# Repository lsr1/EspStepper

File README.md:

# EspStepper

control a [NEMA stepper motor](https://en.wikipedia.org/wiki/Stepper_motor#NEMA_stepper_motors) with [Home Assistant](https://www.home-assistant.io/) using a D1 mini via [ESPHome](https://esphome.io/). 

## Executive Summary
* This project provides a solution for controlling a NEMA stepper motor with Home Assistant (via ESPHome), utilizing a D1 mini board.
* This project consists of a KiCad project that gives you the [Gerber files](gerber/gerber.zip) to order a PCB (e.g. at [JLCPCB](https://cart.jlcpcb.com) onto which (mostly) passive components (pinheaders/sockets) are soldered. Then you plug on some standard modules you can get from [AliExpress](https://www.aliexpress.com), create a device in Home Assistant and are pretty much done.
* For the impatient: Go to [Installation](#Installation).

## Picture

## Sidenotes
This is my second "public GitHub" project (see here my [first one](https://github.com/lsr1/wb2s-to-esp12)). I made something (crude) that I nevertheless think might be useful for somebody else. That is also the reason why this readme will be very long - for myself I want to document the story behind it for my records, and (hopefully) for your pleasure :-) </br>
Despite the verbosity of the README, it assumes that you know how to solder, how to work with a multi meter and your way around Home Assistant and ESPHome. Some things here are weirdly specific, while some are infuriatingly generic (assuming a lot of knowhow).

## Preamble (Why)
* I did this because I wanted an easy way to drive a stepper via Home Assistant. I couldn't find an idiot-proof end2end solution on the whole internet - everything was just pieces. There was just no "easy" way with   all the parts connected (be it SW or HW). So I made <i>this</i>.
* I did this to scratch an itch of mine, and to hone my skills in all the tools along the toolchain. For me, this was really interdisciplinary. 

## Design Decisions (and other reasoning)
### Goals
* Drive exactly one NEMA stepper.
* Have only one input voltage that works for the stepper but also powers the rest of the board. 
* Have mainly only passive components on the PCB to make it easy to solder.
* Use as many widely available off-the-shelf components and modules as possible over working directly with parts/MCUs.
* Have a compact PCB design.
* Don't use jumpers for MS1/2/3 but solder-bridges (uses less space).
* There are already 3 voltages on the board - make them available.
* Enable usage of unused D1 mini pins via pinheaders.
* Have enough GND pins. 
* Have short high-voltage tracks.
* Have everything socketed. 
* Have the antenna of the D1 board protrude over the PCB to avoid interference from PCB copper fill (I didn't want to create a keep-out zone; not for a specific reason - I just wanted to make due w/o one). 
* The silkscreen on the board shall be self-speaking for modules over the usual 'short nomenclature' (e.g. "J1"). 
* C1 for stabilizing voltage when the NEMA stepper turns on should be optional. 
* No SMD components (to make it easier to solder for novices).
* Voltage pins are intentionally not on one continuous pin row but 3x2.
* Low cost.

### Non-goals
* No need for perfectly aligned mounting holes.
* No need for silent steppers (thus use A4988). 
* Micro-USB port of the D1 does not need to be available when socketed.
* No need for energy efficiency. 
* No need for "perfect" PCB/circuit design (<i>done is better than perfect</i>).

## BOM (for 1 module)
* 1 x PCB (see [Installation](#Installation))
* 1 x D1 Mini (with normal pinheaders looking 'down'; from Ali)
* 1 x A4988 stepper driver (from Ali)
* 1 x MP1584 DC-DC step-down Module with LM2596 (from Ali)
* 1 x KF301- 2Pin 5.0mm screw-terminal (from Ali)
* 4 x 1x8pin female pinheaders 2.54 mm (from Ali)
* 4 x 1x2pin female pinheaders 2.54 mm (from Ali)
* standard 1 row 2.54mm male pinheaders
* (optional) 1 x capacitor (>= 12V, THT radial D5.0mm / P2.00mm)

## Installation
This will be long. Brace.

### Order PCBs
* Go to [JLCPCB](https://cart.jlcpcb.com/quote) and upload the [gerber.zip](gerber/gerber.zip). Sidenote: I'm neither sponsored nor do I endorse them specifically, I just find them convenient. Make sure you select the correct PCB thickness (1.2 mm). I also set "Remove Order Number" to "Specify a location" (layout contains a field for this). No other special settings.

### Soldering
* Solder the components. No special advice here - it should be pretty straight forward.
* Close the MS1/2/3 solder bridges for microstepping.
* If you populate the C1 capacitor, make sure you leave enough 'height' of the legs to fold it down 90 degrees to lie flat (otherwise the A4988 won't fit above).

### Tuning
* <b>BEFORE</b> putting on all modules and connect power, tune the MP1584 to 5V output. Do this <b>now</b>.
* The A4988 needs to be tuned to output the correct voltage for your NEMA stepper. I will not document here how to do this - please google it. 

### Assemply
* Put all modules on the board. Take care of the orientation - there is absolutely no safeguard against voltage reversal or such things.
* Usually an A4988 stepper comes with a mini-heatsink. Put it on.
* Provide 12V input (VCC is left on the screw terminal, GND is right).
* If your NEMA stepper cable is connected [like this](photos/NEMA_cabling.png), then the pins go on the board like shown in the table below (however: don't trust this - your stepper might be different, your cable might be different, etc.):

|row #|color|board pin|
---| --- | ---
1|BLK|2B
2|BLU|2A
3|GRN|1B
4|RED|1A

### Software
* It is assumed you have a working instance of Home Assistant with a working ESPHome plugin. If not, please google how to get there.
* Create an ESPHome device in Home Assistant with the configuration as basis noted in [this file](HomeAssistant/my-stepper.yaml). Modify to your gusto.
* Create an automation in Home Assistant with the configuration noted in [this file](HomeAssistant/automation.yaml). Modify to your gusto. Note: The automation includes a slider control that is not documented here. For POC, just run the automation manually.
* If you run the automation (manually), your stepper should turn.
* Read up on the parameters and play around with them - I am intentionally not providing more info or limits or the like. 

### Caveats / FAQ
* This is not the work of a professional, and thus has not been load/fuzzy/destructive-tested. All things could happen, thus this project comes without any warranty. Never use it anywhere in a production situation.

* You can't solder the MP1584 directly on the board even if you don't care about the mouting-hole: The holes for the pins are too small (only the female pin-headers fit, but no the male pinheaders directly). This might be changed on a v2 of the board.

* Todo for v2: Mark the GND pin for the A4988 with silkscreen on the PCB to make it easier to plug in.

* Todo for v2: Mark the diameter of the mounting holes with silkscreen on the PCB. Saves reaching for the caliper.

* Before publishing I got feedback from some dear friends to put ferrit-pearls in series to the 5V for the A4988 and the D1 to make sure the voltage is "clean". I consciously omitted that feedback for simplicity reasons.

* The mounting holes are connected to GND because ... no reason. 

* There is intentionally no ESPHome binary provided for download and flashing here.

* I'm neither affiliated with nor do I get money from JLC nor Ali, I just find both convenient. 

* Why is there no YT video describing this whole thing? - B/c IMHO YT sucks for technical documentation. 

* The KiCad project does not have all components/footprints - I got them from various online sources and didn't track the copyright - sorry.
* I would love to have some useful web GUI in the ESPHome code - but I don't know how to do that. 

## License and Legalese
* May be (re)used for personal/private use only and not sold/licensed for commercial or financial gain. This non-standard license should make it impossible and really difficult for commercial enterprises to profit from my work (pay people to design this!), but enable the hobbyist/enthusiast to work with it.
* If I have inadverently (re-)used your work without either properly attributing it or something, please let me know - I'd be happy to correct this.

## Donations
Yes please.

## Feedback
Also yes please! (I hope I figure out how this whole pull-request thing works...)

## Shoutout ...
* ... to [CCC](https://www.ccc.de) and [CCCZH](https://www.ccczh.ch/)!
* ... to all FOSS contributors that helped making SW that enabled me to do this. Nanos gigantium humeris insidentes.

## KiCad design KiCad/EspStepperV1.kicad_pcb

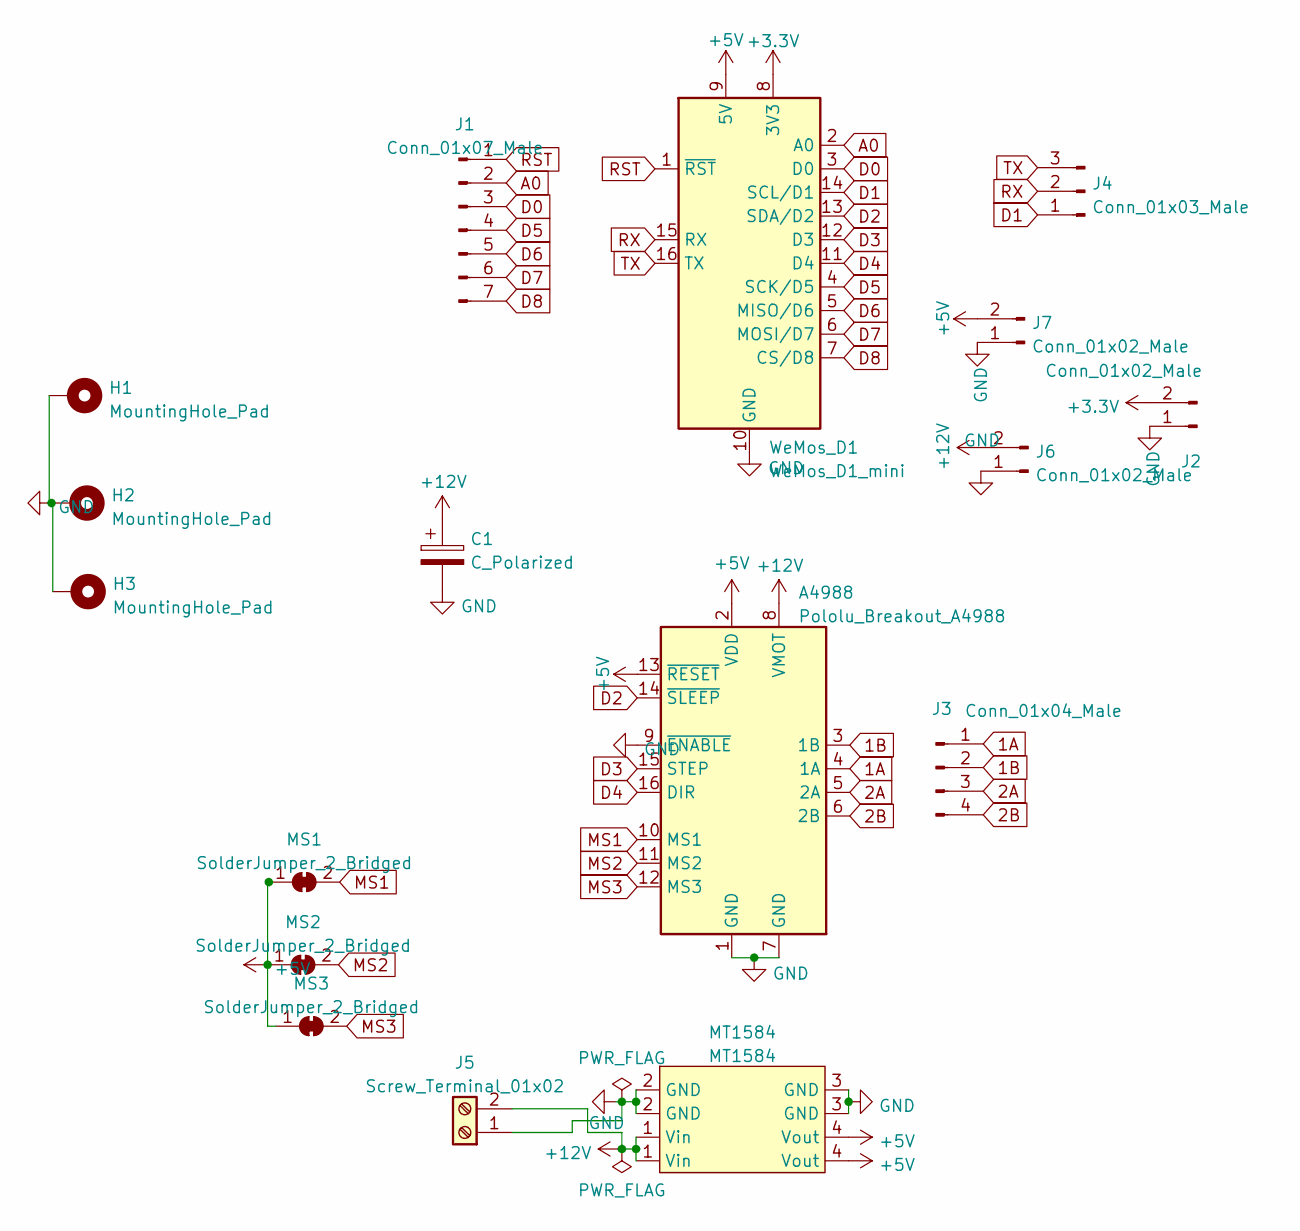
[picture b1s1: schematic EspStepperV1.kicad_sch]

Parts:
A4988: Pololu_Breakout_A4988; Pololu_Breakout-16_15.2x20.3mm
C1: C_Polarized; CP_Radial_D5.0mm_P2.00mm
H1, H2, H3: MountingHole_Pad; MountingHole_2.7mm_M2.5_DIN965_Pad_TopBottom
J1: Conn_01x07_Male; PinHeader_1x07_P2.54mm_Vertical
J2, J6, J7: Conn_01x02_Male; PinHeader_1x02_P2.54mm_Vertical
J3: Conn_01x04_Male; PinHeader_1x04_P2.54mm_Vertical
J4: Conn_01x03_Male; PinHeader_1x03_P2.54mm_Vertical
J5: Screw_Terminal_01x02; TerminalBlock_bornier-2_P5.08mm
MS1, MS2, MS3: SolderJumper_2_Bridged; SolderJumper-2_P1.3mm_Bridged_Pad1.0x1.5mm
MT1584: MT1584; MP1584_buck_module
WeMos_D1: WeMos_D1_mini; WEMOS_D1_mini_light

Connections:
1A: A4988.4 (1A), J3.1
1B: A4988.3 (1B), J3.2
2A: A4988.5 (2A), J3.3
2B: A4988.6 (2B), J3.4
+3V3: J2.2, WeMos_D1.8 (3V3)
+5V: A4988.2 (VDD), A4988.13 (~RESET), J7.2, MS1.1 (A), MS2.1 (A), MS3.1 (A), MT1584.4 (Vout), WeMos_D1.9 (5V)
A0: J1.2, WeMos_D1.2 (A0)
D0: J1.3, WeMos_D1.3 (D0)
D1: J4.1, WeMos_D1.14 (SCL/D1)
D2: A4988.14 (~SLEEP), WeMos_D1.13 (SDA/D2)
D3: A4988.15 (STEP), WeMos_D1.12 (D3)
D4: A4988.16 (DIR), WeMos_D1.11 (D4)
D5: J1.4, WeMos_D1.4 (SCK/D5)
D6: J1.5, WeMos_D1.5 (MISO/D6)
D7: J1.6, WeMos_D1.6 (MOSI/D7)
D8: J1.7, WeMos_D1.7 (CS/D8)
MS1: A4988.10 (MS1), MS1.2 (B)
MS2: A4988.11 (MS2), MS2.2 (B)
MS3: A4988.12 (MS3), MS3.2 (B)
RST: J1.1, WeMos_D1.1 (~RST)
RX: J4.2, WeMos_D1.15 (RX)
TX: J4.3, WeMos_D1.16 (TX)

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
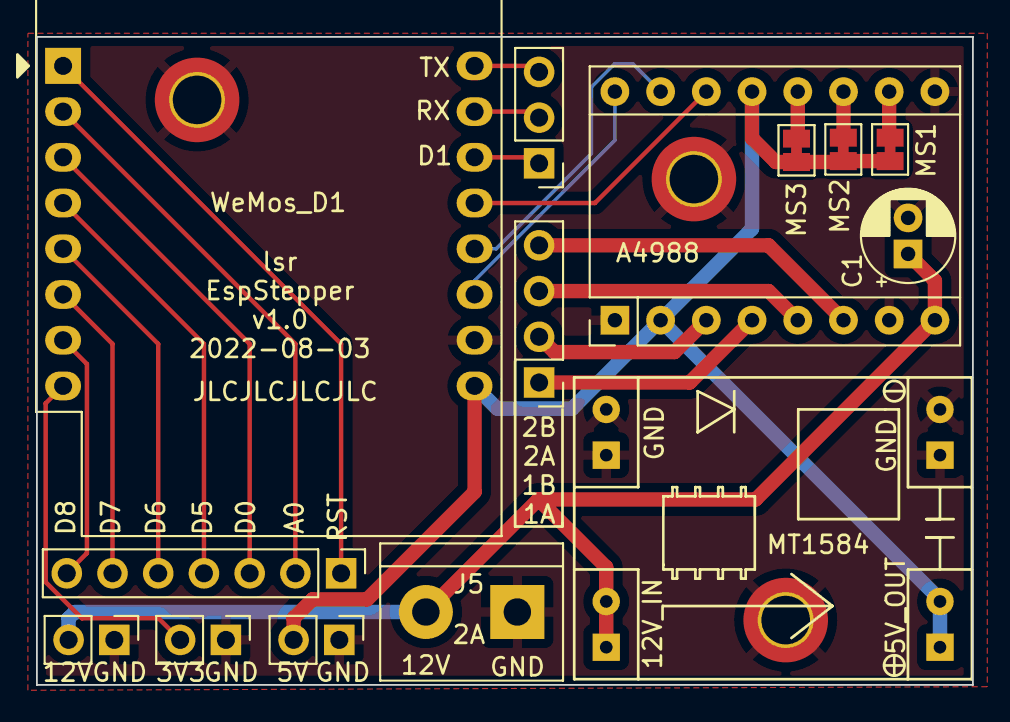
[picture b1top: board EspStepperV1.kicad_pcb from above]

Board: 2 copper layers, 52.0 x 36.0 mm, 17 parts (0 on the bottom side), 24 nets.

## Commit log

2022-09-20 fixed cabling table and better pic
